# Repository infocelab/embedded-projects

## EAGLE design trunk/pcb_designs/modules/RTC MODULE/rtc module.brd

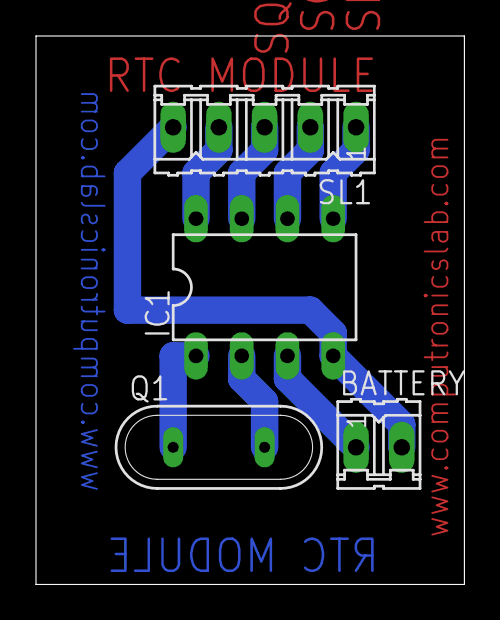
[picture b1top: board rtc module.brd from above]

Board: 2 copper layers, 23.8 x 30.5 mm, 4 parts (0 on the bottom side), 8 nets.

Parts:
BATTERY: 3.3v; 02P
IC1: DS1307; DIL08
Q1: 32KHZ; QS
SL1: 5 pin; 05P

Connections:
unnamed: IC1.1, Q1.1
unnamed: IC1.2, Q1.2
unnamed: IC1.6, SL1.2
unnamed: IC1.7, SL1.3
unnamed: IC1.8, SL1.4
unnamed: BATTERY.1, IC1.3
unnamed: BATTERY.2, IC1.4, SL1.5
unnamed: IC1.5, SL1.1

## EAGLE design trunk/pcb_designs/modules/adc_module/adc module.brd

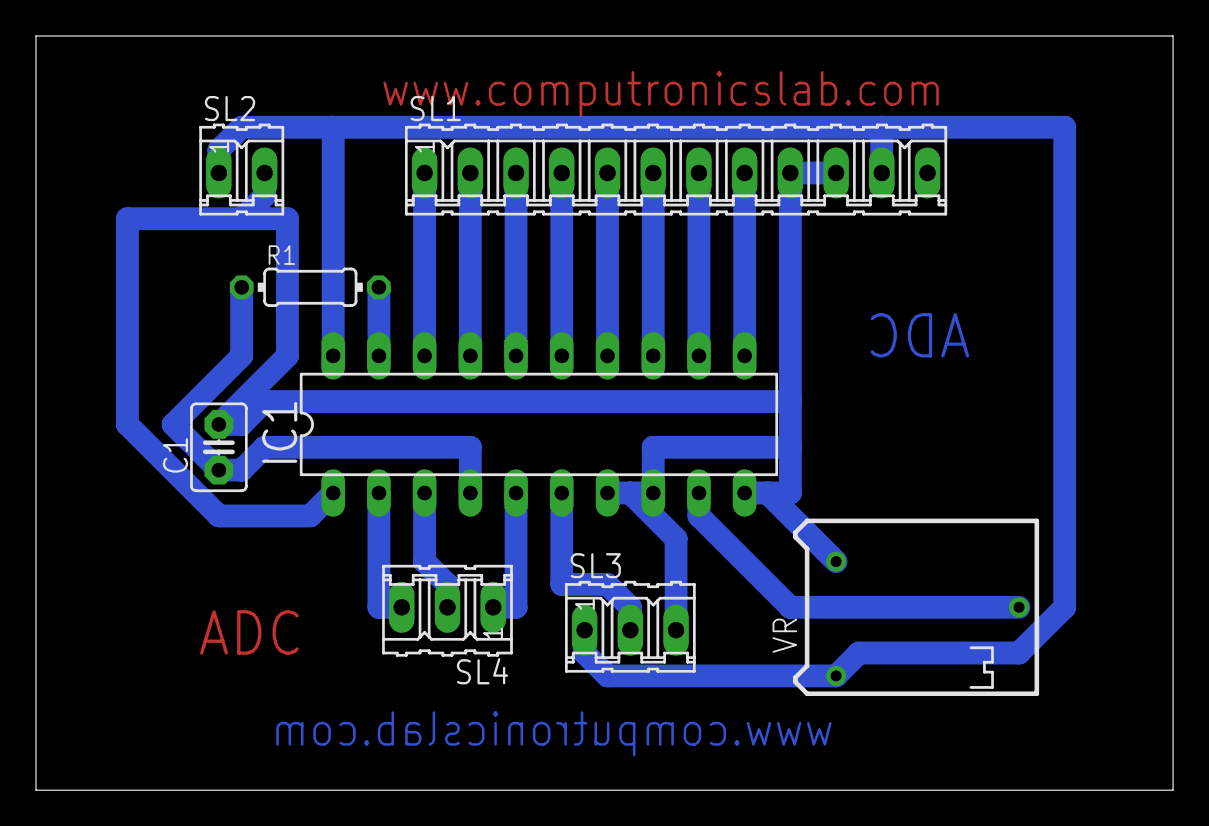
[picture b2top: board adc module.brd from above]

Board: 2 copper layers, 63.2 x 41.9 mm, 8 parts (0 on the bottom side), 17 nets.

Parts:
C1: 150pf; C2.5-3
IC1: adc804; DIL20
R1: 10k; 0204/7
SL1: 12P
SL2: 02P
SL3: LM35; 03P
SL4: 03P
VR: 10k; RTRIM64P

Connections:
unnamed: IC1.18, SL1.1
unnamed: IC1.17, SL1.2
unnamed: IC1.16, SL1.3
unnamed: IC1.15, SL1.4
unnamed: IC1.14, SL1.5
unnamed: IC1.13, SL1.6
unnamed: IC1.12, SL1.7
unnamed: IC1.11, SL1.8
unnamed: IC1.19, R1.2
unnamed: C1.1, IC1.4, R1.1
unnamed: IC1.2, SL4.3
unnamed: IC1.3, SL4.2
unnamed: IC1.6, SL3.2
unnamed: IC1.5, SL4.1
unnamed: IC1.9, VR.2
unnamed: C1.2, IC1.1, IC1.7, IC1.8, IC1.10, SL1.9, SL1.10, SL2.2, SL3.3, VR.3
unnamed: IC1.20, SL1.11, SL2.1, SL3.1, VR.1

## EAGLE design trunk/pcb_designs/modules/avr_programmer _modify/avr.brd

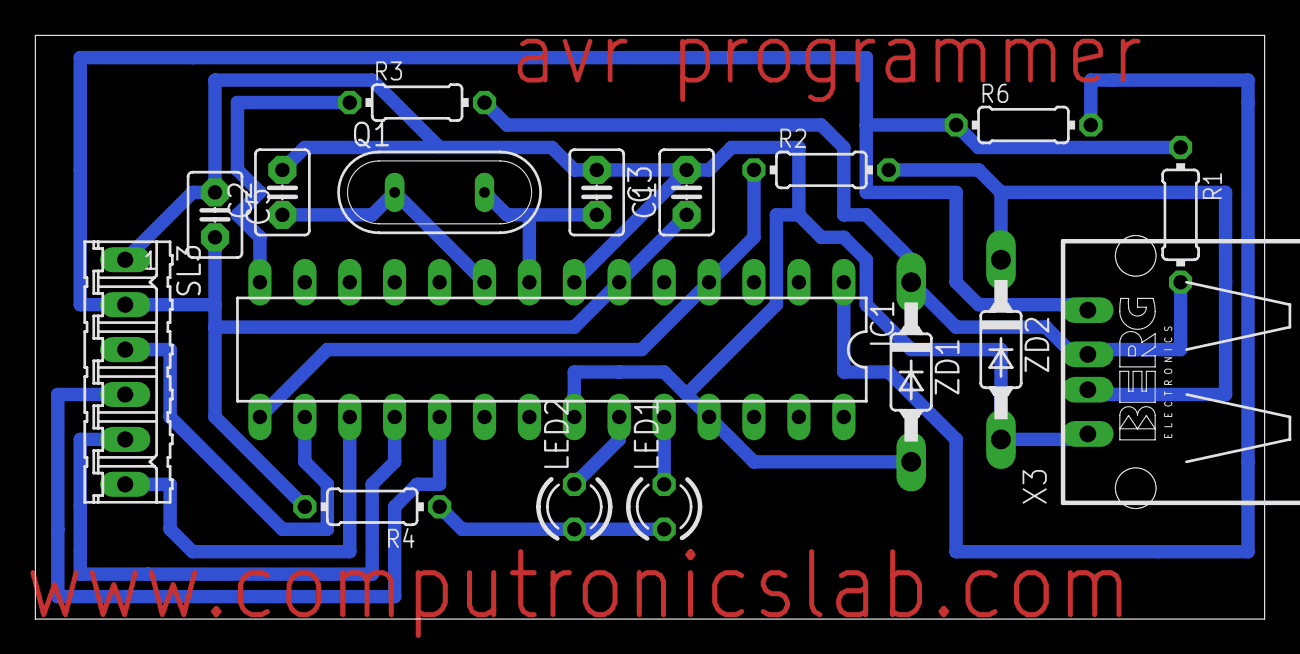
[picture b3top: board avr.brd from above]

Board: 2 copper layers, 69.5 x 33.0 mm, 17 parts (0 on the bottom side), 16 nets.

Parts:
C1, C5: 0.1uf; C2.5-3
C2, C3: 22pf; C2.5-3
IC1: QT9701BD; DIL28-3
LED1: 3mm; LED3MM
LED2: 5mm; LED3MM
Q1: 12 MHZ; QS
R1: 2.6k; 0204/7
R2, R3: 70E; 0204/7
R4: 1K; 0204/7
R6: 10K; 0204/7
SL3: 06P
X3: PN87520
ZD1, ZD2: 3.6v; SOD81

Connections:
unnamed: C3.2, IC1.8, Q1.2
unnamed: C2.1, IC1.9, Q1.1
unnamed: C1.2, C2.2, C3.1, C5.1, IC1.7, IC1.22, IC1.25, SL3.1, X3.1, ZD1.A, ZD2.A
unnamed: IC1.24, LED1.K
unnamed: IC1.23, LED2.K
unnamed: R2.2, X3.2, ZD2.C
unnamed: C1.1, C5.2, IC1.6, R1.1, R4.2, R6.1, SL3.2, X3.4
unnamed: IC1.4, IC1.15, R2.1
unnamed: R1.2, R3.2, X3.3, ZD1.C
unnamed: LED1.A, LED2.A, R4.1
unnamed: IC1.14, R3.1
unnamed: IC1.1, R6.2
unnamed: IC1.17, SL3.6
unnamed: IC1.16, SL3.3
unnamed: IC1.18, SL3.5
unnamed: IC1.19, SL3.4

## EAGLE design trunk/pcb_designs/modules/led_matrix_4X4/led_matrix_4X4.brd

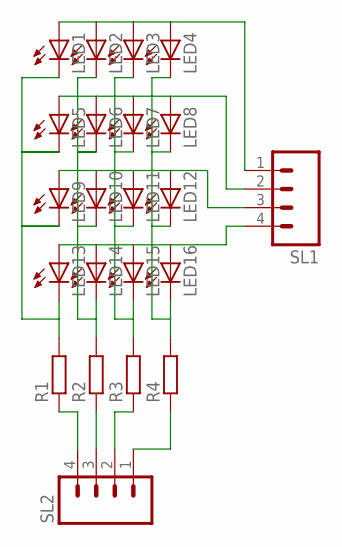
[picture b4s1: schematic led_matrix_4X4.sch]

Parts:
LED1, LED2, LED3, LED4, LED5, LED6, LED7, LED8, LED9, LED10, LED11, LED12, LED13, LED14, LED15, LED16: LED5MM
R1, R2, R3, R4: R-EU_0204/7; 0204/7
SL1, SL2: M04; 04P

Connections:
unnamed: LED1.K (C), LED5.K (C), LED9.K (C), LED13.K (C), R1.2
unnamed: R1.1, SL2.4
unnamed: R2.1, SL2.3
unnamed: R3.1, SL2.2
unnamed: R4.1, SL2.1
unnamed: LED1.A, LED2.A, LED3.A, LED4.A, SL1.1
unnamed: LED5.A, LED6.A, LED7.A, LED8.A, SL1.2
unnamed: LED9.A, LED10.A, LED11.A, LED12.A, SL1.3
unnamed: LED13.A, LED14.A, LED15.A, LED16.A, SL1.4
unnamed: LED2.K (C), LED6.K (C), LED10.K (C), LED14.K (C), R2.2
unnamed: LED3.K (C), LED7.K (C), LED11.K (C), LED15.K (C), R3.2
unnamed: LED4.K (C), LED8.K (C), LED12.K (C), LED16.K (C), R4.2

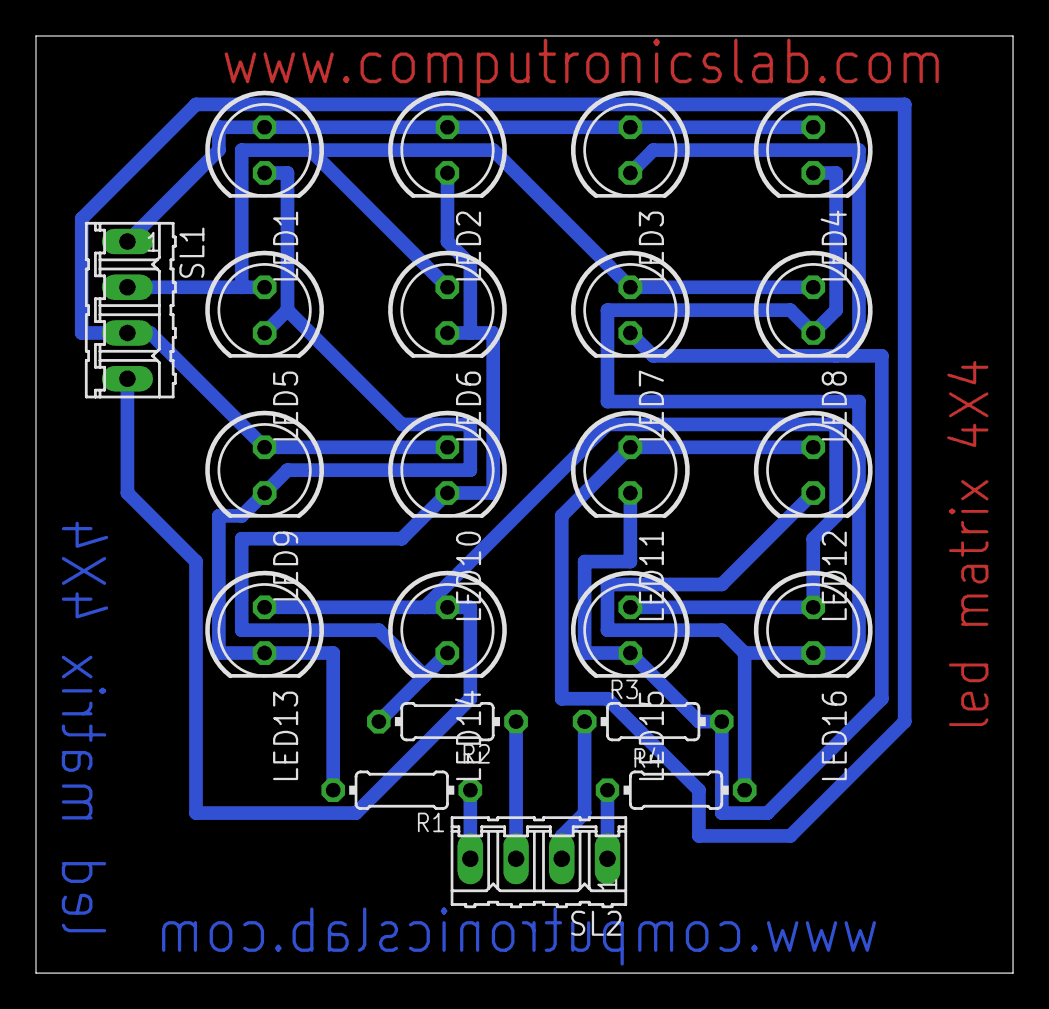
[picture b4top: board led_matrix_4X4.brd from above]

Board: 2 copper layers, 54.3 x 52.1 mm, 22 parts (0 on the bottom side), 12 nets.

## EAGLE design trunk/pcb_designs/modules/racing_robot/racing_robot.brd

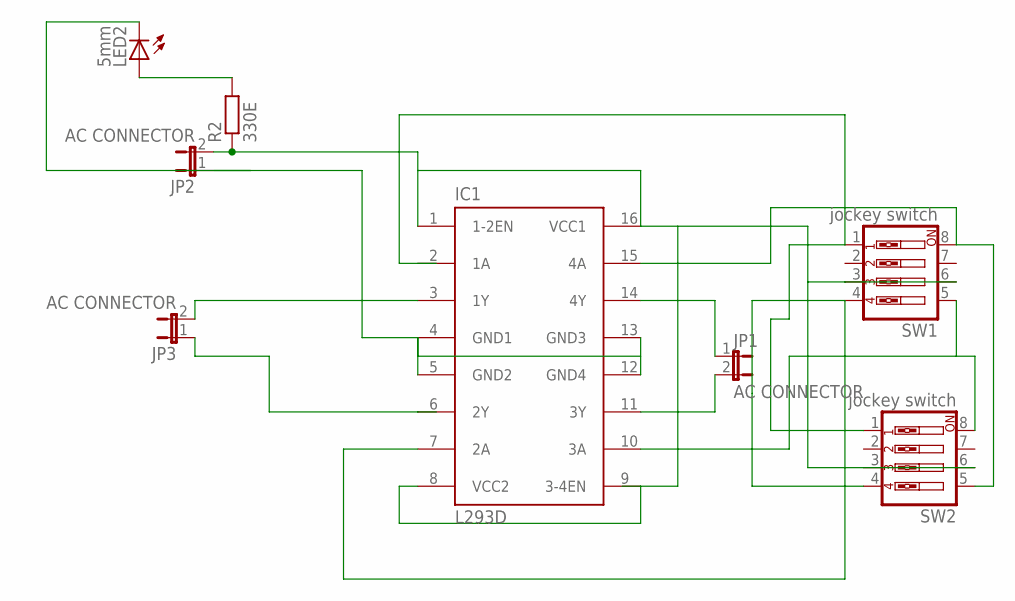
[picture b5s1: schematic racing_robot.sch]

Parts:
IC1: L293D; DIL16
JP1, JP2, JP3: AC CONNECTOR; JP1
LED2: 5mm; LED_LD260
R2: 330E; 0204/7
SW1, SW2: jockey switch; EDG-04

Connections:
unnamed: LED2.A, R2.2
unnamed: IC1.4 (GND1), IC1.5 (GND2), IC1.12 (GND4), IC1.13 (GND3), JP2.1, LED2.K (C)
unnamed: IC1.2 (1A), SW1.1, SW2.1
unnamed: IC1.6 (2Y), JP3.1
unnamed: IC1.3 (1Y), JP3.2
unnamed: IC1.14 (4Y), JP1.1
unnamed: IC1.11 (3Y), JP1.2
unnamed: IC1.15 (4A), SW1.8, SW2.5
unnamed: IC1.7 (2A), SW1.4, SW2.4
unnamed: IC1.10 (3A), SW1.5, SW2.8
unnamed: IC1.1 (1-2EN), IC1.8 (VCC2), IC1.9 (3-4EN), IC1.16 (VCC1), JP2.2, R2.1, SW1.3, SW1.6, SW2.3, SW2.6

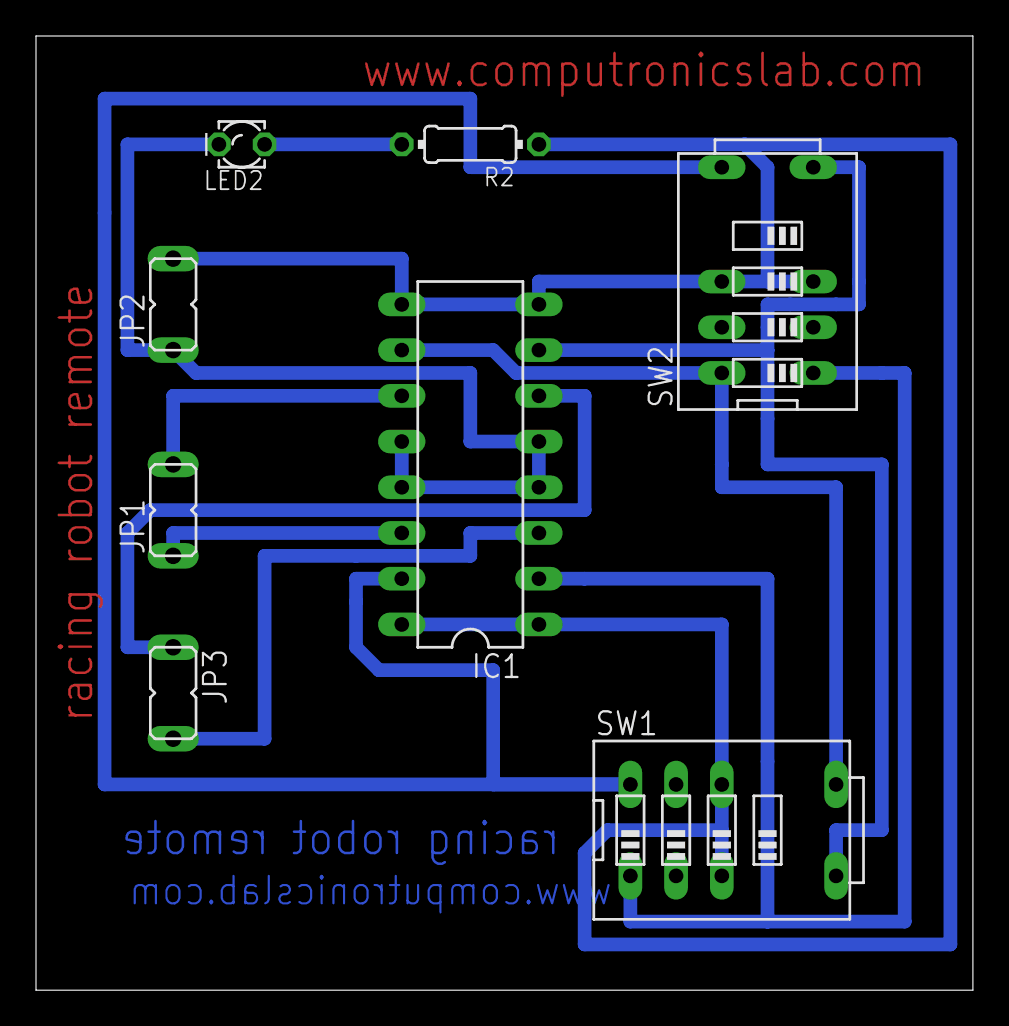
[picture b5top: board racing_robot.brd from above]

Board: 2 copper layers, 52.1 x 53.0 mm, 8 parts (0 on the bottom side), 11 nets.

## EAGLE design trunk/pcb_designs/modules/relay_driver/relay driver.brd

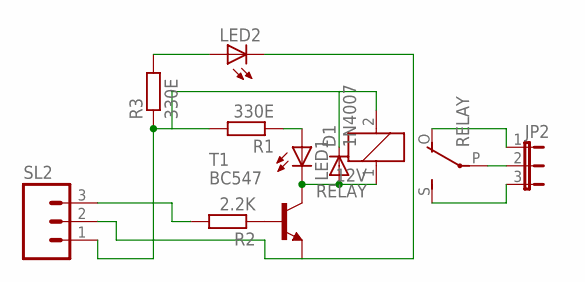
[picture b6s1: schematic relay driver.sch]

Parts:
D1: 1N4007; DO41-10
JP2: JP2E; JP2
LED1, LED2: LED3MM
R1, R3: 330E; 0204/7
R2: 2.2K; 0204/7
RELAY: 12V; G5LE
SL2: M03; 03P
T1: BC547; TO92

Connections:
unnamed: D1.A, LED1.K (C), RELAY.1, T1.3 (C)
unnamed: JP2.2, RELAY.P
unnamed: LED1.A, R1.1
unnamed: R2.1, T1.2 (B)
unnamed: LED2.K (C), SL2.2, T1.1 (E)
unnamed: D1.C, R1.2, R3.1, RELAY.2, SL2.1
unnamed: R2.2, SL2.3
unnamed: JP2.3, RELAY.S
unnamed: LED2.A, R3.2
unnamed: JP2.1, RELAY.O

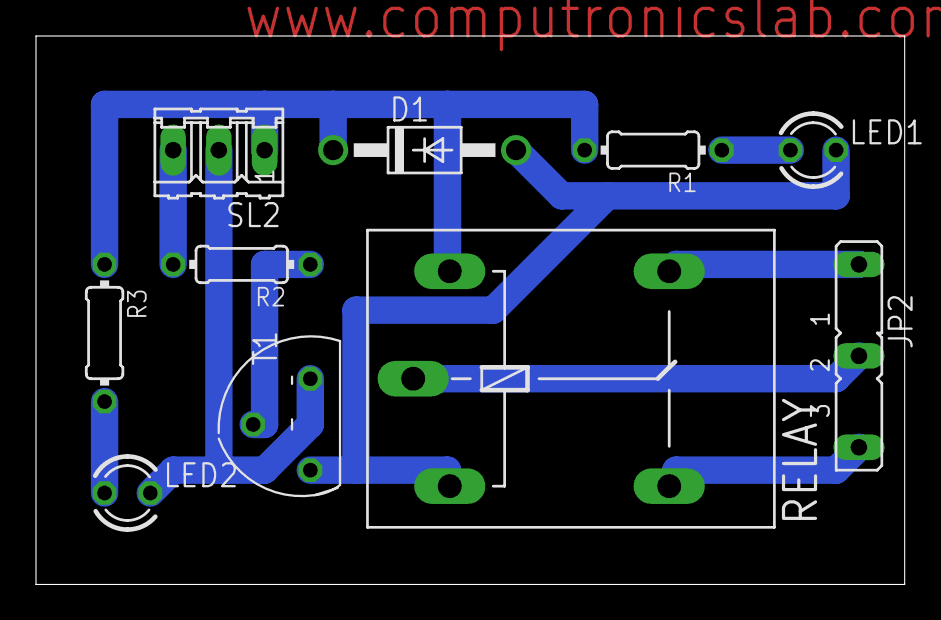
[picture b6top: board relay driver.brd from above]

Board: 2 copper layers, 48.3 x 30.5 mm, 10 parts (0 on the bottom side), 10 nets.

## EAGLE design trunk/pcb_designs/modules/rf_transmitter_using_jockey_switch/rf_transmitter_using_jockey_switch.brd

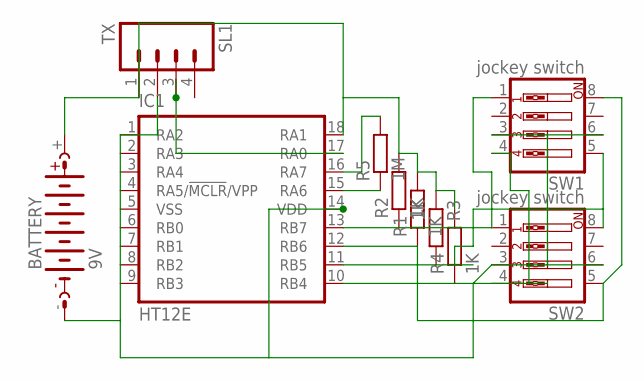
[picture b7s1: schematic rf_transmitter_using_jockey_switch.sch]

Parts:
BATTERY: 9V; AB9V
IC1: HT12E; DIL18
R1, R2, R3, R4: 1K; 0204/7
R5: 1M; 0204/7
SL1: TX; 04P
SW1, SW2: jockey switch; EDG-04

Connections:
unnamed: IC1.10 (RB4), R4.1, SW1.4, SW2.4
unnamed: IC1.11 (RB5), R3.2, SW1.5, SW2.8
unnamed: IC1.12 (RB6), R1.1, SW1.8, SW2.5
unnamed: IC1.13 (RB7), R2.1, SW1.1, SW2.1
unnamed: IC1.15 (RA6), R5.1
unnamed: IC1.16 (RA7), R5.2
unnamed: BATTERY.+, IC1.18 (RA1), R1.2, R2.2, R3.1, R4.2, SL1.1
unnamed: BATTERY.-, IC1.1 (RA2), IC1.2 (RA3), IC1.3 (RA4), IC1.4 (RA5/!MCLR!/VPP), IC1.5 (VSS), IC1.6 (RB0), IC1.7 (RB1), IC1.8 (RB2), IC1.9 (RB3), IC1.14 (VDD), SL1.2, SW1.3, SW1.6, SW2.3, SW2.6
unnamed: IC1.17 (RA0), SL1.3

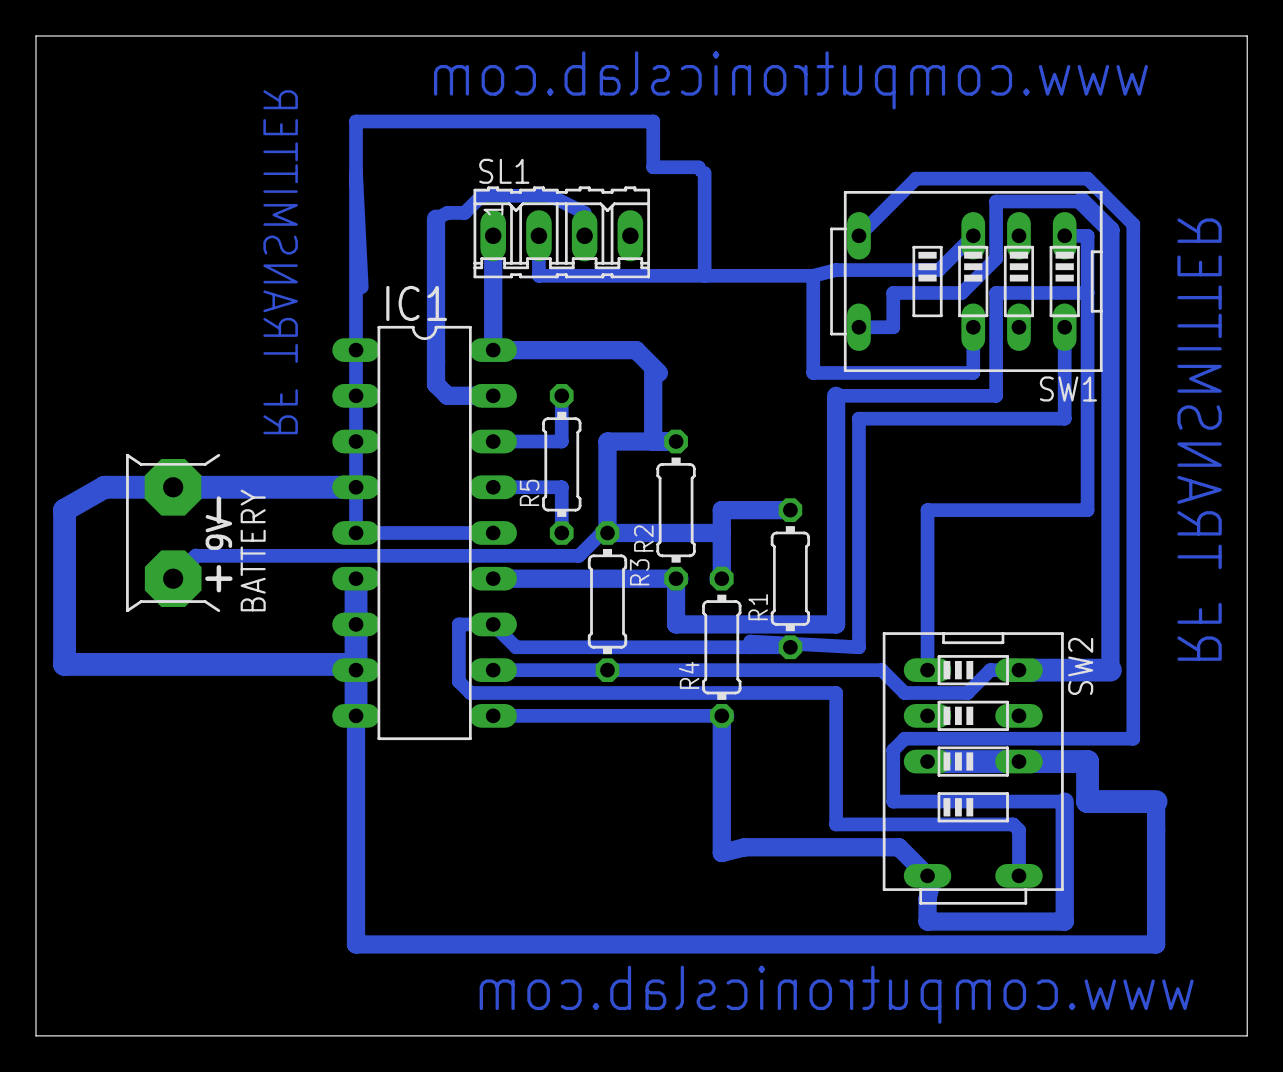
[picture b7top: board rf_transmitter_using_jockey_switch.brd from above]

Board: 2 copper layers, 67.3 x 55.6 mm, 10 parts (0 on the bottom side), 9 nets.

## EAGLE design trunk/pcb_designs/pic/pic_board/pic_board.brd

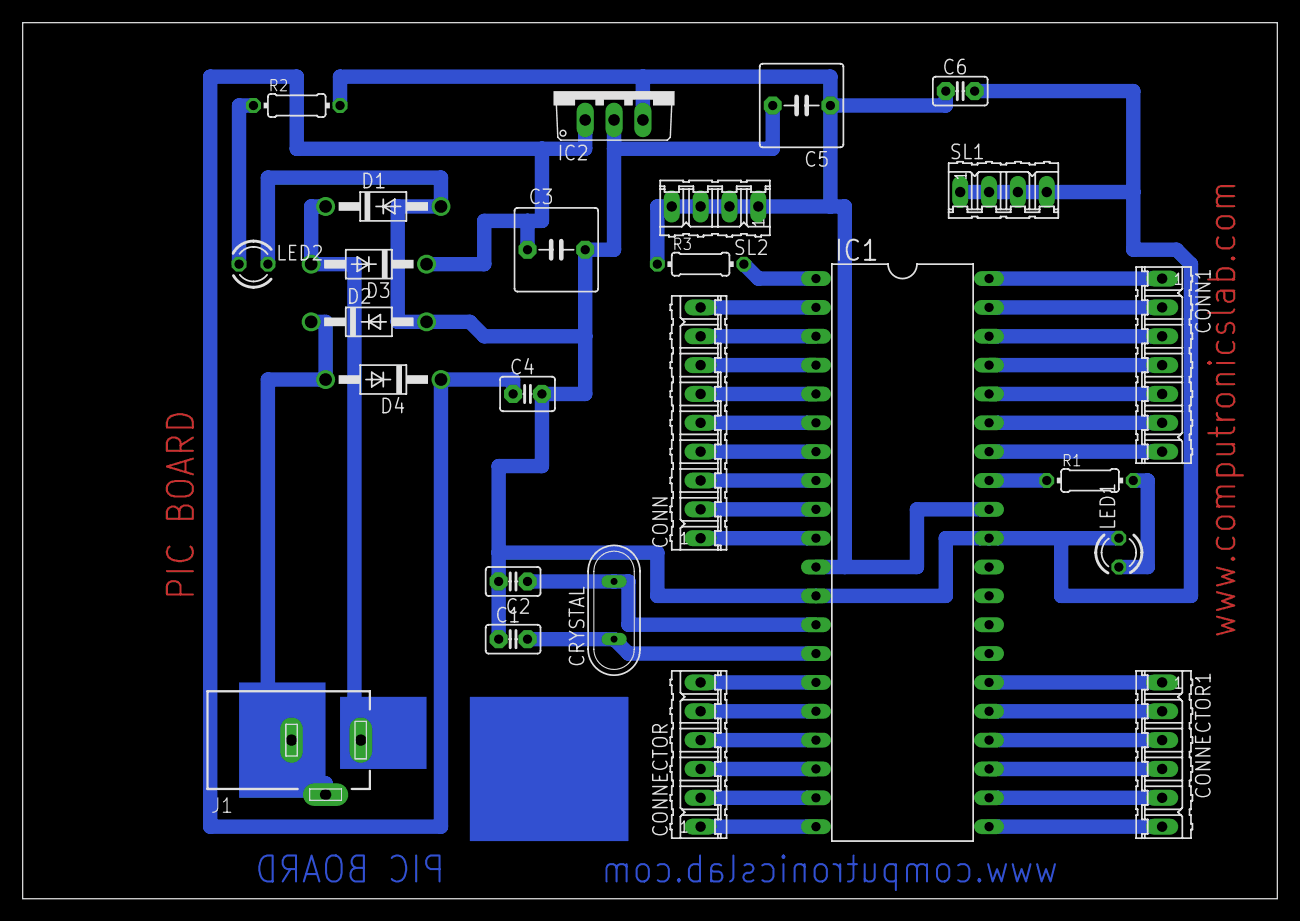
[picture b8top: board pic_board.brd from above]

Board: 2 copper layers, 110.5 x 77.1 mm, 25 parts (0 on the bottom side), 39 nets.

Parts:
C1, C2, C6: 22pf; C2.5-2
C3: 1000uf; C5B7.2
C4: 0.1uf; C2.5-3
C5: 100uf; C5B7.2
CONN: 9 pin; 09P
CONN1: 7 pin; 07P
CONNECTOR, CONNECTOR1: 6 pin; 06P
CRYSTAL: 8MHZ; QS
D1, D2, D3, D4: 1N4007; DO41-10
IC1: PIC16f877a; DIL40
IC2: 7805TV; TO220V
J1: DCJ0303
LED1, LED2: 3mm; LED3MM
R1, R2: 220E; 0204/7
R3: 10K; 0204/7
SL1, SL2: 4 pin; 04P

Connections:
unnamed: C2.1, CRYSTAL.2, IC1.13
unnamed: C1.2, CRYSTAL.1, IC1.14
unnamed: LED1.A, R1.2
unnamed: CONN.1, IC1.10
unnamed: CONN.2, IC1.9
unnamed: CONN.3, IC1.8
unnamed: CONN.4, IC1.7
unnamed: CONN.5, IC1.6
unnamed: CONN.6, IC1.5
unnamed: CONN.7, IC1.4
unnamed: CONN.8, IC1.3
unnamed: CONN.9, IC1.2
unnamed: CONNECTOR.1, IC1.20
unnamed: CONNECTOR.2, IC1.19
unnamed: CONNECTOR.3, IC1.18
unnamed: CONNECTOR.4, IC1.17
unnamed: CONNECTOR.5, IC1.16
unnamed: CONNECTOR.6, IC1.15
unnamed: CONN1.1, IC1.40
unnamed: CONN1.2, IC1.39
unnamed: CONN1.3, IC1.38
unnamed: CONN1.4, IC1.37
unnamed: CONN1.5, IC1.36
unnamed: CONN1.6, IC1.35
unnamed: CONN1.7, IC1.34
unnamed: CONNECTOR1.1, IC1.26
unnamed: CONNECTOR1.2, IC1.25
unnamed: CONNECTOR1.3, IC1.24
unnamed: IC1.33, R1.1
unnamed: C3.1, C4.1, D3.C, D4.C, IC2.1
unnamed: D2.C, D4.A, J1.2, J1.3
unnamed: D1.C, D3.A, J1.1
unnamed: C5.1, C6.1, IC1.11, IC1.32, IC2.3, R2.2, R3.1, SL2.1, SL2.2, SL2.3, SL2.4
unnamed: LED2.A, R2.1
unnamed: C1.1, C2.2, C3.2, C4.2, C5.2, C6.2, D1.A, D2.A, IC1.12, IC1.31, IC2.2, LED1.K, LED2.K, SL1.1, SL1.2, SL1.3, SL1.4
unnamed: CONNECTOR1.4, IC1.23
unnamed: CONNECTOR1.5, IC1.22
unnamed: CONNECTOR1.6, IC1.21
unnamed: IC1.1, R3.2
